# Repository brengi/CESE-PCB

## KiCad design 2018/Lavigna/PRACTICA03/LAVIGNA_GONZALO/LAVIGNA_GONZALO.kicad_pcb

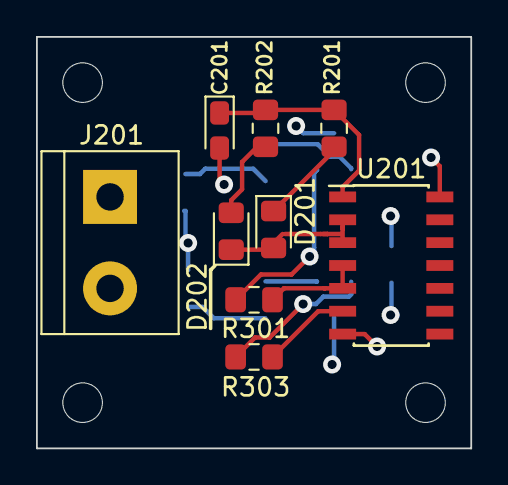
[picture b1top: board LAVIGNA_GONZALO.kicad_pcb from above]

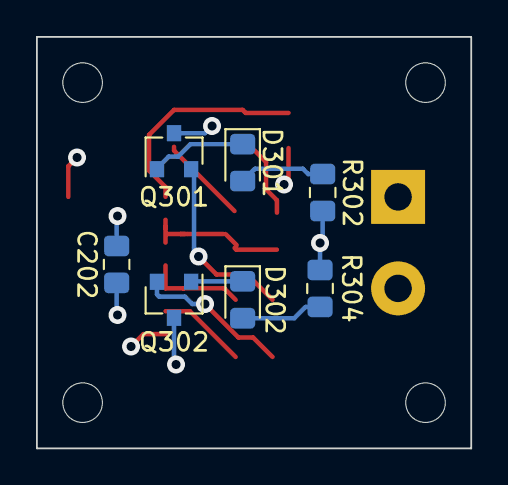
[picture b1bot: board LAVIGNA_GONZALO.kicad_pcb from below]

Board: 4 copper layers, 24.1 x 22.9 mm, 20 parts (7 on the bottom side), 14 nets.

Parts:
C201: CP; CP_EIA-2012-12_Kemet-R_Pad1.30x1.05mm_HandSolder
C202: 0.1u; C_0805_2012Metric_Pad1.15x1.40mm_HandSolder
D201, D202: 1N4148; D_0805_2012Metric_Pad1.15x1.40mm_HandSolder
D301, D302: LED ROJO; D_0805_2012Metric_Pad1.15x1.40mm_HandSolder
J201: Conn_01x02; TerminalBlock_bornier-2_P5.08mm
MH101, MH102, MH103, MH104: MountingHole; MountingHole_2.2mm_M2
Q301, Q302: BC546; SOT-23
R201, R202: 100K; R_0805_2012Metric_Pad1.15x1.40mm_HandSolder
R301, R303: 2K2; R_0805_2012Metric_Pad1.15x1.40mm_HandSolder
R302, R304: 470R; R_0805_2012Metric_Pad1.15x1.40mm_HandSolder
U201: 40106; SOIC-14_3.9x8.7mm_P1.27mm

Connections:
+5V: C202.1, J201.2, R302.2, R304.2, U201.14
/Circuito con leds/LED1: R301.2, U201.4, U201.5
/Circuito con leds/LED2: R303.2, U201.6
GND: C201.2, C202.2, J201.1, Q301.3, Q302.3, U201.7
unnamed: C201.1, R201.2, R202.2, U201.1
unnamed: D201.1, R201.1
unnamed: D201.2, D202.1, U201.2, U201.3
unnamed: D202.2, R202.1
unnamed: D301.1, Q301.1
unnamed: D301.2, R302.1
unnamed: D302.1, Q302.1
unnamed: D302.2, R304.1
unnamed: Q301.2, R301.1
unnamed: Q302.2, R303.1

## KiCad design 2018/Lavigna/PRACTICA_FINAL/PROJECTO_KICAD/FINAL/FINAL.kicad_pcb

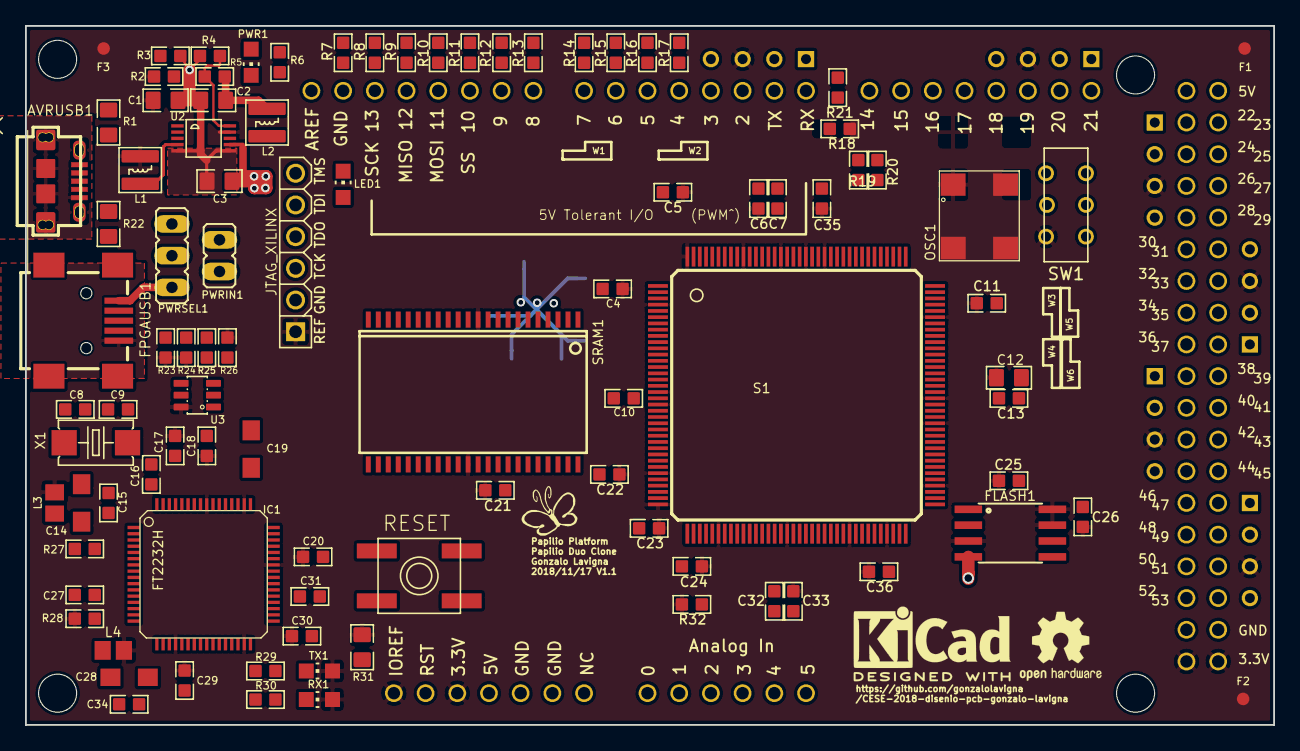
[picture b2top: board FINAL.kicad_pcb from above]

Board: 4 copper layers, 100.0 x 56.0 mm, 120 parts (0 on the bottom side), 160 nets.

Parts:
AVRUSB1: MYCON2_USB-MINI-B; CON2_USB_MICRO_B_AT
C1, C2: 22u/6V3; 0805
C3: 10uF/10V; 0805
C4, C5, C6, C7, C10, C11, C13, C15, C16, C17, C18, C20, C21, C22, C23, C24, C25, C26, C27, C29, C30, C31, C32, C33, C34, C35, C36: 0.1uF; 0603
C8, C9: 27pF; 0603
C12: 0.1uF; 0805
C14, C28: 4.7uF; SMC_A
C19: 3.3uF; SMC_A
C101, C102, C105: 100nF; 0603
C103, C104: 1uF; 0603
C106, C107: 22pF; 0603
F1, F2, F3: Fiducial; Fiducial_1mm_Dia_2mm_Outer
FLASH1: FLASH-SPI-25XXSMD1; SO08-EIAJ
FPGAUSB1: CONN_USB; CONN_USB_MINI-B
IC1: FT2232H; LQFP64
L1, L2: 3.3uH; VLS3015
L3, L4: FERRITE_BEAD603; FB603
L100: MH2029-300Y; 0805
LED1: Yellow; CHIP-LED0805
LOGO1: Logo_Open_Hardware_Small; OSHW-Logo2_7.3x6mm_SilkScreen
LOGO2: logo_glavigna; KiCad-Logo2_6mm_SilkScreen
OSC1: 32MHz; OSC1
PWR1: Green; CHIP-LED0805
PWRIN1: JP1E; JP1
PWRSEL1: JP2E; JP2
R1, R22: 22R; 0805
R2: 6K8 1%; 0603
R3, R4, R5: 1K5 1%; 0603
R6: 1K8; 0603
R7, R32: 4.7K; 0603
R8, R9, R10, R11, R12, R13, R14, R15, R16, R17, R18, R19, R20, R21: 390; 0603
R23, R24, R26, R28, R110: 10K; 0603
R25: 2.2K; 0603
R27: 12K 1%; 0603
R29, R30: 1K; 0603
R31: 47K; 0805
R109: 1M; 0603
RESET: EVQQ2; EVQ-Q2
RX1: LEDCHIP-LED0805; CHIP-LED0805
S1: 6SLX9TQG144; TQ144
SRAM1: ISSI_SRAM_8BIT; TSOP44-II
SW1: SWITCH-2CH-6P-3010010P1; 6P-2CH-2.54-9.1X3.5X3.2+2H
TX1: LEDCHIP-LED0805; CHIP-LED0805
U1: ARDUINO_MEGA_SHIELD
U2: LTC3419MS; MSOP10
U3: 93C56B; SOT23-6
U101: ATMEGA32U4-XUMU; QFN44ML7X7
U$1: JTAG_XILINX; JTAG
U$3, U$3#2, U$3#3, U$3#4: STAND-OFF-TIGHT
U$7: GADGETFACTORY_LOGO
WING_POWER1, WING_POWER2, WING_POWER3, WING_POWER4, WING_POWER5, WING_POWER6: FRAME-A4L-LOC; POWER_NO_TEXT
X1: 12MHz; 4X6
Y1: 16Mhz KX-7; CRYSTAL-3.2-2.5

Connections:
+1V2: C2.1, C7.1, C10.1, C13.1, C32.1, L2.2, R5.2, S1.19, S1.28, S1.52, S1.89, S1.128
+1V8: C16.1, C19.+, C27.1, C31.1, IC1.12, IC1.37, IC1.49, IC1.64
+3V3: C1.1, C4.1, C5.1, C6.1, C11.1, C12.1, C17.1, C18.1, C20.1, C21.1, C22.1, C23.1, C24.1, C25.1, C26.1, C29.1, C30.1, C33.1, C35.1, C36.1, C101.2, C105.2, FLASH1.3, FLASH1.7, FLASH1.8, IC1.20, IC1.31, IC1.42, IC1.50, IC1.56, L1.2, L3.2, L4.2, L100.2, OSC1.1@1, OSC1.4@4, R2.2, R23.1, R24.1, R26.1, R28.1, R31.2, R32.1, R110.2, RX1.A, S1.4, S1.18, S1.20, S1.31, S1.36, S1.42, S1.53, S1.63, S1.69, S1.76, S1.86, S1.90, S1.103, S1.122, S1.125, S1.129, S1.135, S1.144, SRAM1.11, SRAM1.33, SW1.CH2A, TX1.A, U1.3.3V, U1.3V3@1, U1.3V3@2, U1.IOREF, U2.9, U3.6, U101.2, U101.14, U101.34, U$1.JTAG_REF, WING_POWER1.P3, WING_POWER2.P3, WING_POWER3.P3, WING_POWER4.P3, WING_POWER5.P3, WING_POWER6.P3
+5V: C3.1, PWRIN1.1, PWRSEL1.2, R6.1, U1.5V@0, U1.5V@1, U1.5V@2, U2.2, U2.3, U2.7, WING_POWER1.P4, WING_POWER2.P4, WING_POWER3.P4, WING_POWER4.P4, WING_POWER5.P4, WING_POWER6.P4
/Arduino/5V_ARDUINO: AVRUSB1.P1, PWRSEL1.3, U101.7
/Arduino/ARD_RESET: R110.1, S1.139, U1.RES, U101.13
/Arduino/AREF: C102.1, U1.AREF, U101.42
/Arduino/ATMEGA_A0: U1.A0, U101.41
/Arduino/ATMEGA_A1: U1.A1, U101.40
/Arduino/ATMEGA_IO13*: R7.2, U101.9
/Arduino/AVCC: C104.1, L100.1, U101.24, U101.44
/Arduino/AVRUSB_N: R1.1, U101.3
/Arduino/AVRUSB_P: R22.1, U101.4
/Arduino/D+: AVRUSB1.P3, R22.2
/Arduino/D-: AVRUSB1.P2, R1.2
/Arduino/MEGA_D14: S1.115, U1.D14, U101.30
/Arduino/MEGA_D15: S1.114, U1.D15, U101.31
/Arduino/MEGA_D16: S1.112, U1.D16, U101.32
/Arduino/MEGA_D28/A5: S1.88, U1.A5, U1.D28, U101.36
/Arduino/MEGA_D30/A4: S1.85, U1.A4, U1.D30, U101.37
/Arduino/MEGA_D32/A3: S1.83, U1.A3, U1.D32, U101.38
/Arduino/MEGA_D34/A2: S1.81, U1.A2, U1.D34, U101.39
/Arduino/UCAP: C103.1, U101.6
/Arduino/XTAL1: C107.2, R109.1, U101.17, Y1.1
/Arduino/XTAL2: C106.2, R109.2, U101.16, Y1.3
/FPGA/AD0-JTAG_TCK: IC1.16, S1.109, U$1.JTAG_TCK
/FPGA/AD1-JTAG_TDI: IC1.17, S1.110, U$1.JTAG_TDI
/FPGA/AD2-JTAG_TDO: IC1.18, S1.106, U$1.JTAG_TDO
/FPGA/AD3-JTAG_TMS: IC1.19, S1.107, U$1.JTAG_TMS
/FPGA/AD4-DTR: IC1.21, S1.45
/FPGA/BD0_TXD/MPSSE_TCK: IC1.38, S1.46
/FPGA/BD1_RXD/MPSSE_TDI: IC1.39, S1.141
/FPGA/BD2_MPSSE_TDO: IC1.40, S1.140
/FPGA/BD3_MPSSE_TMS: IC1.41, S1.138
/FPGA/BD4-DTR: IC1.43, S1.137
/FPGA/FPGA-CORE/FLASH_CS: FLASH1.1, S1.38
/FPGA/FPGA-CORE/FLASH_SCK: FLASH1.6, S1.70
/FPGA/FPGA-CORE/FLASH_SI: FLASH1.5, S1.64
/FPGA/FPGA-CORE/FLASH_SO: FLASH1.2, S1.65
/FPGA/FPGA-CORE/MEGA_D0: R21.2, S1.116
/FPGA/FPGA-CORE/MEGA_D1: R20.2, S1.117
/FPGA/FPGA-CORE/MEGA_D2: R19.2, S1.118
/FPGA/FPGA-CORE/MEGA_D3: R18.2, S1.119
/FPGA/FPGA-CORE/MEGA_D4: R17.2, S1.120
/FPGA/FPGA-CORE/MEGA_D5: R16.2, S1.121
/FPGA/FPGA-CORE/MEGA_D6: R15.2, S1.123
/FPGA/FPGA-CORE/MEGA_D7: R14.2, S1.124
/FPGA/FPGA-CORE/MEGA_D8: R13.2, S1.126
/FPGA/FPGA-CORE/MEGA_D9: R12.2, S1.127
/FPGA/FPGA-CORE/MEGA_D10: R11.2, S1.131
/FPGA/FPGA-CORE/MEGA_D11: R10.2, S1.132
/FPGA/FPGA-CORE/MEGA_D12: R9.2, S1.133
/FPGA/FPGA-CORE/MEGA_D13: R8.2, S1.134
/FPGA/FPGA-CORE/MEGA_D17: S1.111, U1.D17
/FPGA/FPGA-CORE/MEGA_D18: S1.105, U1.D18
/FPGA/FPGA-CORE/MEGA_D19: S1.102, U1.D19
/FPGA/FPGA-CORE/MEGA_D20: S1.101, U1.D20
/FPGA/FPGA-CORE/MEGA_D21: S1.100, U1.D21
/FPGA/FPGA-CORE/MEGA_D22: S1.99, U1.D22
/FPGA/FPGA-CORE/MEGA_D23: S1.98, U1.D23
/FPGA/FPGA-CORE/MEGA_D24: S1.97, U1.D24
/FPGA/FPGA-CORE/MEGA_D25: S1.95, U1.D25
/FPGA/FPGA-CORE/MEGA_D26: S1.93, U1.D26
/FPGA/FPGA-CORE/MEGA_D27: S1.92, U1.D27
/FPGA/FPGA-CORE/MEGA_D29: S1.87, U1.D29
/FPGA/FPGA-CORE/MEGA_D31: S1.84, U1.D31
/FPGA/FPGA-CORE/MEGA_D33: S1.82, U1.D33
/FPGA/FPGA-CORE/MEGA_D35: S1.80, U1.D35
/FPGA/FPGA-CORE/MEGA_D36: S1.79, U1.D36
/FPGA/FPGA-CORE/MEGA_D37: S1.78, U1.D37
/FPGA/FPGA-CORE/MEGA_D38: S1.75, U1.D38
/FPGA/FPGA-CORE/MEGA_D39: S1.74, U1.D39
/FPGA/FPGA-CORE/MEGA_D40: S1.67, U1.D40
/FPGA/FPGA-CORE/MEGA_D41: S1.66, U1.D41
/FPGA/FPGA-CORE/MEGA_D42: S1.62, U1.D42
/FPGA/FPGA-CORE/MEGA_D43: S1.61, U1.D43
/FPGA/FPGA-CORE/MEGA_D44: S1.59, U1.D44
/FPGA/FPGA-CORE/MEGA_D45: S1.58, U1.D45
/FPGA/FPGA-CORE/MEGA_D46: S1.57, U1.D46
/FPGA/FPGA-CORE/MEGA_D47: S1.56, U1.D47
/FPGA/FPGA-CORE/MEGA_D48: S1.55, U1.D48
/FPGA/FPGA-CORE/MEGA_D49: S1.51, U1.D49
/FPGA/FPGA-CORE/MEGA_D50: S1.50, U1.D50
/FPGA/FPGA-CORE/MEGA_D51: S1.48, U1.D51
/FPGA/FPGA-CORE/MEGA_D52: S1.47, U1.D52
/FPGA/FPGA-CORE/MEGA_D53: R32.2, S1.39, U1.D53
/FPGA/FPGA-CORE/OSC_IN: OSC1.3@3, S1.94
/FPGA/FPGA-CORE/SRAM_A0: S1.7, SRAM1.3
/FPGA/FPGA-CORE/SRAM_A1: S1.8, SRAM1.4
/FPGA/FPGA-CORE/SRAM_A2: S1.9, SRAM1.5
/FPGA/FPGA-CORE/SRAM_A3: S1.10, SRAM1.6
/FPGA/FPGA-CORE/SRAM_A4: S1.11, SRAM1.7
/FPGA/FPGA-CORE/SRAM_A5: S1.5, SRAM1.16
/FPGA/FPGA-CORE/SRAM_A6: S1.2, SRAM1.17
/FPGA/FPGA-CORE/SRAM_A7: S1.1, SRAM1.18
/FPGA/FPGA-CORE/SRAM_A8: S1.143, SRAM1.19
/FPGA/FPGA-CORE/SRAM_A9: S1.142, SRAM1.20
/FPGA/FPGA-CORE/SRAM_A10: S1.43, SRAM1.26
/FPGA/FPGA-CORE/SRAM_A11: S1.41, SRAM1.27
/FPGA/FPGA-CORE/SRAM_A12: S1.40, SRAM1.28
/FPGA/FPGA-CORE/SRAM_A13: S1.35, SRAM1.29
/FPGA/FPGA-CORE/SRAM_A14: S1.34, SRAM1.30
/FPGA/FPGA-CORE/SRAM_A15: S1.27, SRAM1.38
/FPGA/FPGA-CORE/SRAM_A16: S1.29, SRAM1.39
/FPGA/FPGA-CORE/SRAM_A17: S1.33, SRAM1.40
/FPGA/FPGA-CORE/SRAM_A18: S1.32, SRAM1.41
/FPGA/FPGA-CORE/SRAM_A19: S1.44, SRAM1.25
/FPGA/FPGA-CORE/SRAM_A20: S1.30, SRAM1.42
/FPGA/FPGA-CORE/SRAM_D0: S1.14, SRAM1.9
/FPGA/FPGA-CORE/SRAM_D1: S1.15, SRAM1.10
/FPGA/FPGA-CORE/SRAM_D2: S1.16, SRAM1.13
/FPGA/FPGA-CORE/SRAM_D3: S1.17, SRAM1.14
/FPGA/FPGA-CORE/SRAM_D4: S1.21, SRAM1.31
/FPGA/FPGA-CORE/SRAM_D5: S1.22, SRAM1.32
/FPGA/FPGA-CORE/SRAM_D6: S1.23, SRAM1.35
/FPGA/FPGA-CORE/SRAM_D7: S1.24, SRAM1.36
/FPGA/FPGA-CORE/SW1: S1.104, SW1.COM2
/FPGA/FPGA-CORE/~SRAM_CS: S1.12, SRAM1.8
/FPGA/FPGA-CORE/~SRAM_OE: S1.26, SRAM1.37
/FPGA/FPGA-CORE/~SRAM_WE: S1.6, SRAM1.15
/FT2232H/5V_FT2232: FPGAUSB1.VUSB, PWRSEL1.1
/FT2232H/BC3: IC1.54, R30.2
/FT2232H/BC4: IC1.55, R29.2
/FT2232H/EECLK: IC1.62, U3.4
/FT2232H/EECS: IC1.63, R23.2, R24.2, U3.5
/FT2232H/EEDATA: IC1.61, R25.1, U3.3
/FT2232H/FTUSB_N: FPGAUSB1.D-, IC1.7
/FT2232H/FTUSB_P: FPGAUSB1.D+, IC1.8
/FT2232H/~RESET: IC1.14, R28.2
GND: AVRUSB1.P5, AVRUSB1.S1, AVRUSB1.S2, AVRUSB1.S3, AVRUSB1.S4, AVRUSB1.S5, AVRUSB1.S6, C1.2, C2.2, C3.2, C4.2, C6.2, C7.2, C8.2, C9.2, C10.2, C11.2, C12.2, C13.2, C14.-, C15.2, C16.2, C17.2, C18.2, C19.-, C20.2, C21.2, C23.2, C24.2, C25.2, C27.2, C28.-, C29.2, C30.2, C31.2, C32.2, C33.2, C34.2, C35.2, C101.1, C102.2, C103.2, C104.2, C105.1, C106.1, C107.1, FLASH1.4, FPGAUSB1.GND, IC1.1, IC1.5, IC1.10, IC1.11, IC1.13, IC1.15, IC1.25, IC1.35, IC1.47, IC1.51, LED1.C, OSC1.2@2, PWR1.C, PWRIN1.2, R3.2, R4.2, R27.2, RESET.B, RESET.B', S1.3, S1.13, S1.25, S1.49, S1.54, S1.60, S1.68, S1.73, S1.77, S1.91, S1.96, S1.108, S1.113, S1.130, S1.136, SRAM1.12, SRAM1.34, SW1.CH2B, U1.GND@0, U1.GND@1, U1.GND@2, U1.GND@3, U1.GND@4, U2.5, U2.6, U3.2, U101.5, U101.15, U101.23, U101.33, U101.35, U101.43, U101.EXP, WING_POWER1.P1, WING_POWER2.P1, WING_POWER3.P1, WING_POWER4.P1, WING_POWER5.P1, WING_POWER6.P1, Y1.2, Y1.4
unnamed: C8.1, IC1.3, X1.2
unnamed: C9.1, IC1.2, X1.1
unnamed: C14.+, C15.1, C28.+, C34.1, IC1.4, L3.1
unnamed: C5.2, C22.2, C26.2, C36.2
unnamed: IC1.6, R27.1
unnamed: IC1.9, L4.1
unnamed: L1.1, U2.4
unnamed: L2.1, U2.8
unnamed: LED1.A, R7.1
unnamed: PWR1.A, R6.2
unnamed: R2.1, R3.1, U2.1
unnamed: R4.1, R5.1, U2.10
unnamed: R8.1, U1.D13
unnamed: R9.1, U1.D12
unnamed: R10.1, U1.D11
unnamed: R11.1, U1.D10
unnamed: R12.1, U1.D9
unnamed: R13.1, U1.D8
unnamed: R14.1, U1.D7
unnamed: R15.1, U1.D6
unnamed: R16.1, U1.D5
unnamed: R17.1, U1.D4
unnamed: R18.1, U1.D3
unnamed: R19.1, U1.D2
unnamed: R20.1, U1.TX
unnamed: R21.1, U1.RX
unnamed: R25.2, R26.2, U3.1
unnamed: R29.1, TX1.C
unnamed: R30.1, RX1.C
unnamed: R31.1, RESET.A, RESET.A', S1.37

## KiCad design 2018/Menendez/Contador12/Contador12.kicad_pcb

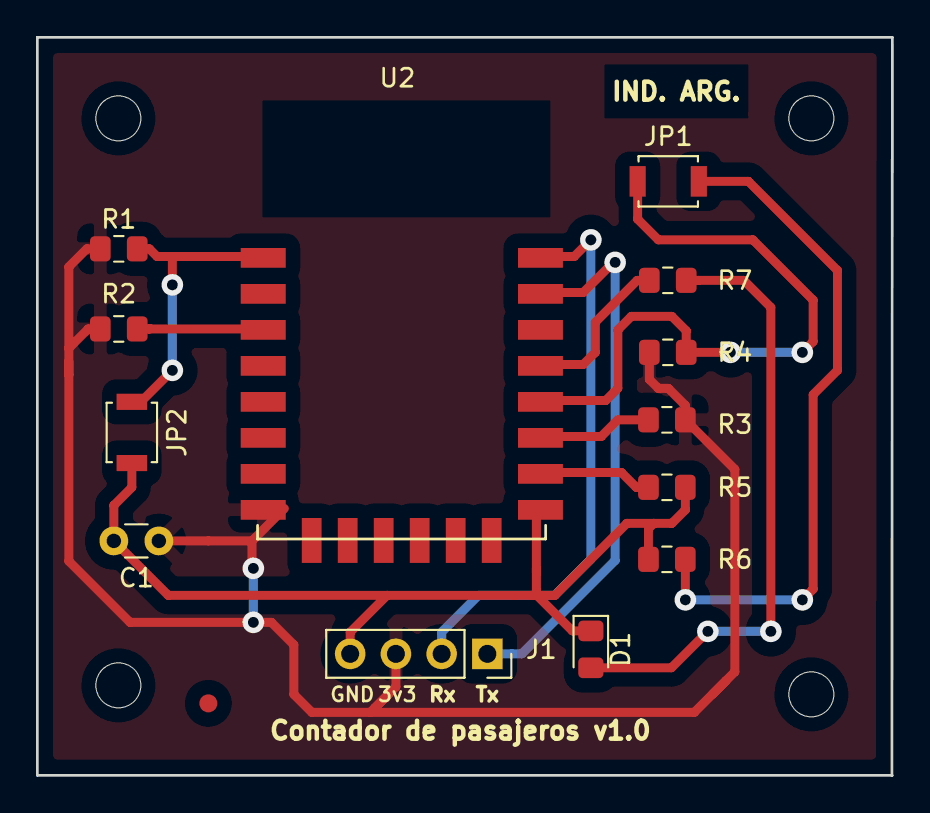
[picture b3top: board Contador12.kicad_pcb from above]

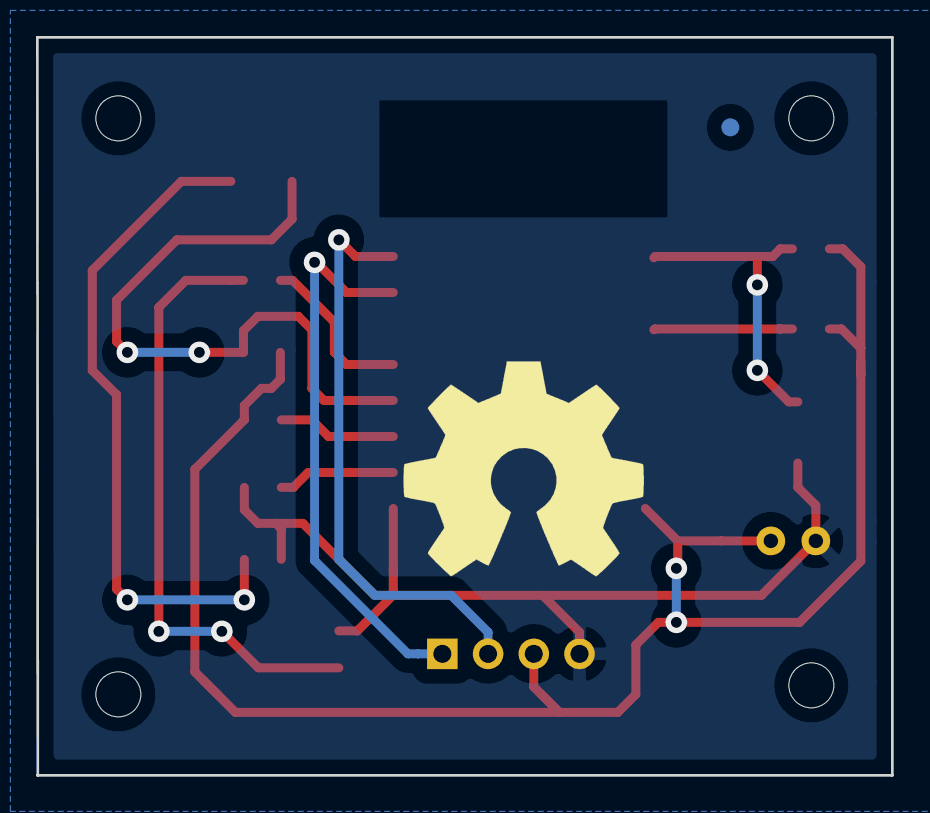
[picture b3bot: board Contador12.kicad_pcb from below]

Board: 2 copper layers, 47.5 x 41.0 mm, 20 parts (2 on the bottom side), 12 nets.

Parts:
C1: 100n; C_Disc_D3.0mm_W1.6mm_P2.50mm
D1: LED; LED_0805_2012Metric_Pad1.15x1.40mm_HandSolder
F1, F2: MH2; Fiducial_1mm_Dia_2mm_Outer
J1: Conector_ESP; PinSocket_1x04_P2.54mm_Vertical
JP1, JP2: Jumper; SW_SPST_B3U-1000P
Logo1: Logo_Open_Hardware_Small; OSHW-Symbol_13.4x12mm_SilkScreen
MH1: MH1; MountingHole_2.5mm
MH2: MH2; MountingHole_2.5mm
MH3: MH3; MountingHole_2.5mm
MH4: MH4; MountingHole_2.5mm
R1, R2, R3, R4, R5: 10k; R_0805_2012Metric_Pad1.15x1.40mm_HandSolder
R6, R7: 470; R_0805_2012Metric_Pad1.15x1.40mm_HandSolder
U2: ESP-12E; ESP-12E_SMD

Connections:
+3V3: C1.1, J1.3, R1.1, R2.2, R3.2, R4.1, U2.8
/Program: JP1.1, R4.2, U2.12
/Reset: JP2.1, R1.2, U2.1
/Rx: J1.2, U2.16
/Tx: J1.1, U2.15
GND: C1.2, D1.1, J1.4, JP2.2, R5.2, R6.2, U2.9
unnamed: D1.2, R7.2
unnamed: JP1.2, R6.1
unnamed: R2.1, U2.3
unnamed: R3.1, U2.11
unnamed: R5.1, U2.10
unnamed: R7.1, U2.13

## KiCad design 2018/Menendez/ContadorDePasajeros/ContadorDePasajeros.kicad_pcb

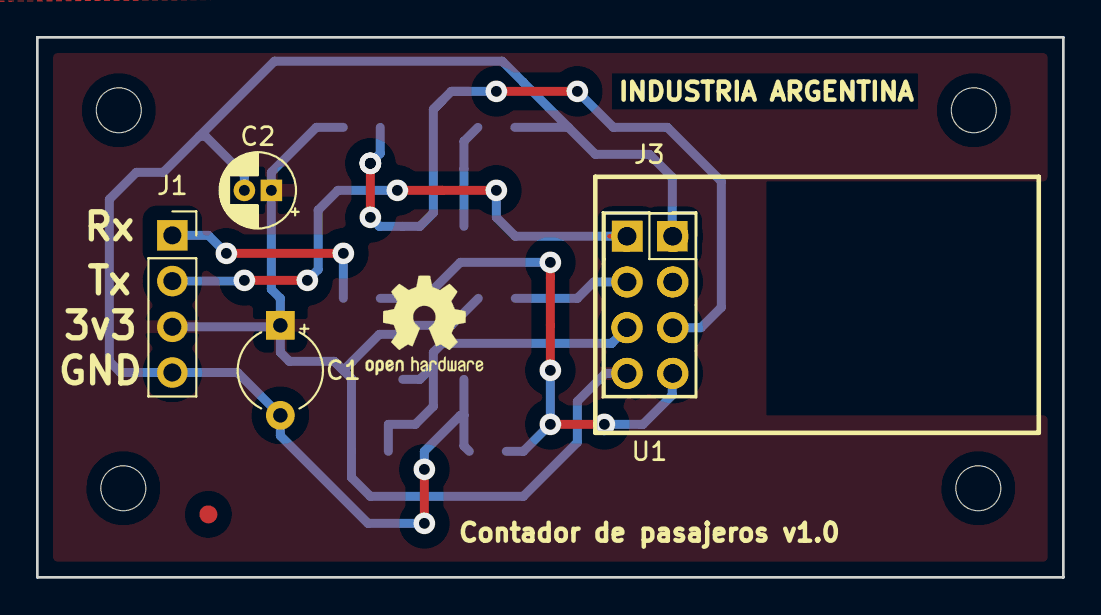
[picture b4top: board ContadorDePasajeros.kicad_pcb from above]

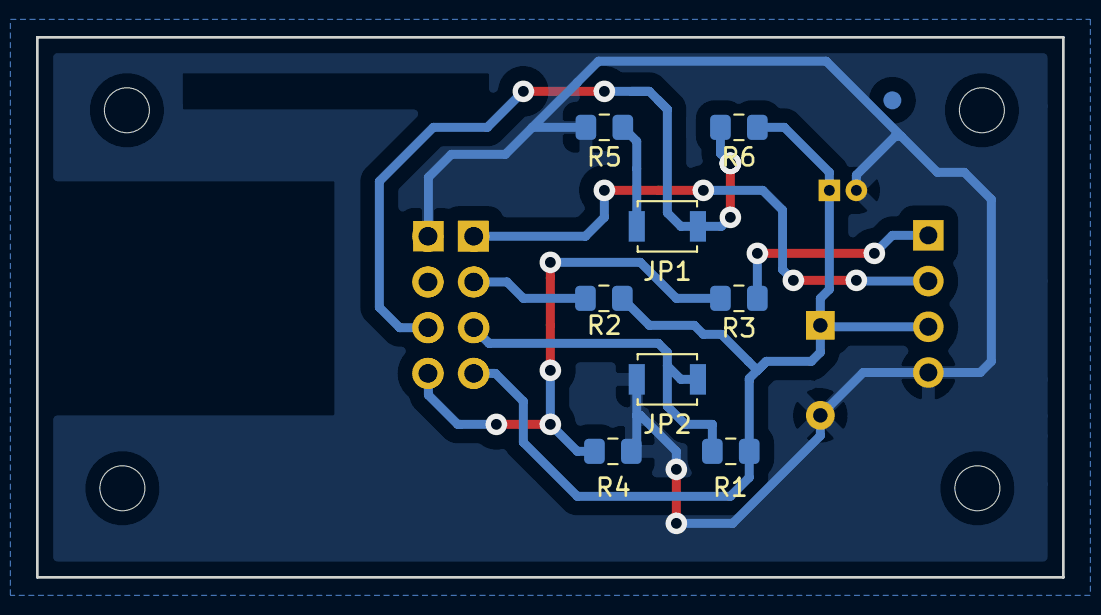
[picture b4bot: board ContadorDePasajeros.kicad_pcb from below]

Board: 2 copper layers, 57.0 x 30.0 mm, 20 parts (9 on the bottom side), 10 nets.

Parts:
C1: 100n; CP_Radial_Tantal_D4.5mm_P5.00mm
C2: 100u; CP_Radial_D4.0mm_P1.50mm
F1, F2: MH4; Fiducial_1mm_Dia_2mm_Outer
J1: Conector_in; PinSocket_1x04_P2.54mm_Vertical
J3: Conector_esp; PinSocket_2x04_P2.54mm_Vertical
JP1, JP2: Jumper; SW_SPST_B3U-1000P
Logo1: Logo_Open_Hardware_Small; OSHW-Logo2_7.3x6mm_SilkScreen
MH1: MH1; MountingHole_2.5mm
MH2: MH2; MountingHole_2.5mm
MH3: MH3; MountingHole_2.5mm
MH4: MH4; MountingHole_2.5mm
R1, R2, R6: 3k3; R_0805_2012Metric_Pad1.15x1.40mm_HandSolder
R3: 1k; R_0805_2012Metric_Pad1.15x1.40mm_HandSolder
R4: 2k; R_0805_2012Metric_Pad1.15x1.40mm_HandSolder
R5: 470; R_0805_2012Metric_Pad1.15x1.40mm_HandSolder
U1: ESP01; ESP-01

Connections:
+3V3: C1.1, C2.1, J1.3, J3.8, R1.2, R2.2, R6.1, U1.7
/Ch: J3.4, R2.1, U1.3
/Gpio0: J3.5, JP1.1, R6.2, U1.6
/Gpio2: J3.3, U1.4
/Rs: J3.6, JP2.1, R1.1, U1.5
/Rx_i: J3.7, R3.2, R4.1, U1.8
GND: C1.2, C2.2, J1.4, J3.1, JP2.2, R4.2, R5.2, U1.2
unnamed: JP1.2, R5.1
Rx: J1.1, R3.1
Tx: J1.2, J3.2, U1.1

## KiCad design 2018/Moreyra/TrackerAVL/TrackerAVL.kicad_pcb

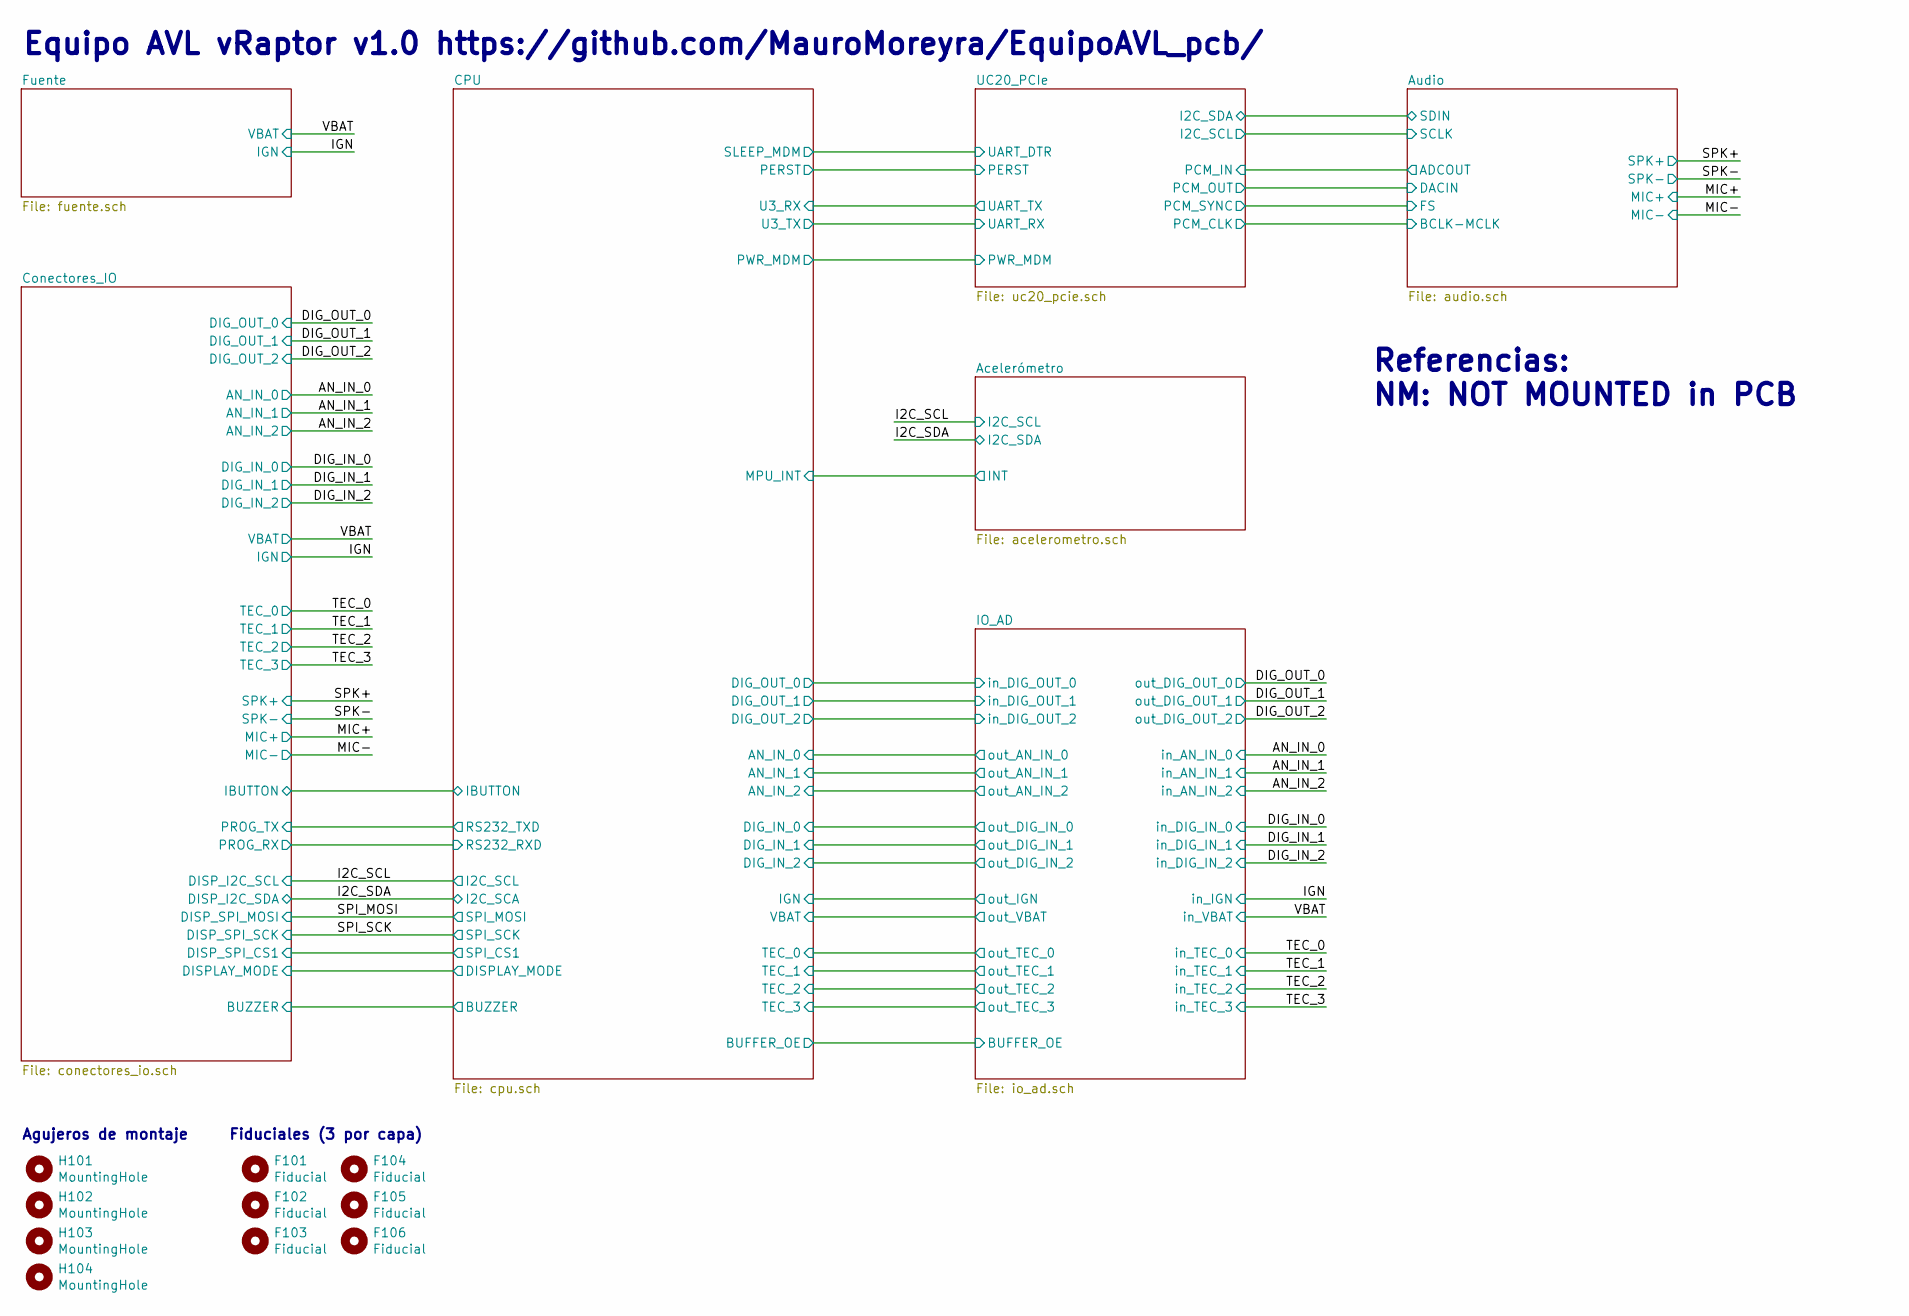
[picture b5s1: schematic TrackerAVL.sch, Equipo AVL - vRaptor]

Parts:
F101, F102, F103, F104, F105, F106: Fiducial; Fiducial_1mm_Dia_2mm_Outer
H101, H102, H103, H104: MountingHole; MountingHole_3.2mm_M3

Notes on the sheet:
Equipo AVL vRaptor v1.0 https://github.com/MauroMoreyra/EquipoAVL_pcb/
Referencias: NM: NOT MOUNTED in PCB
Agujeros de montaje
Fiduciales (3 por capa)

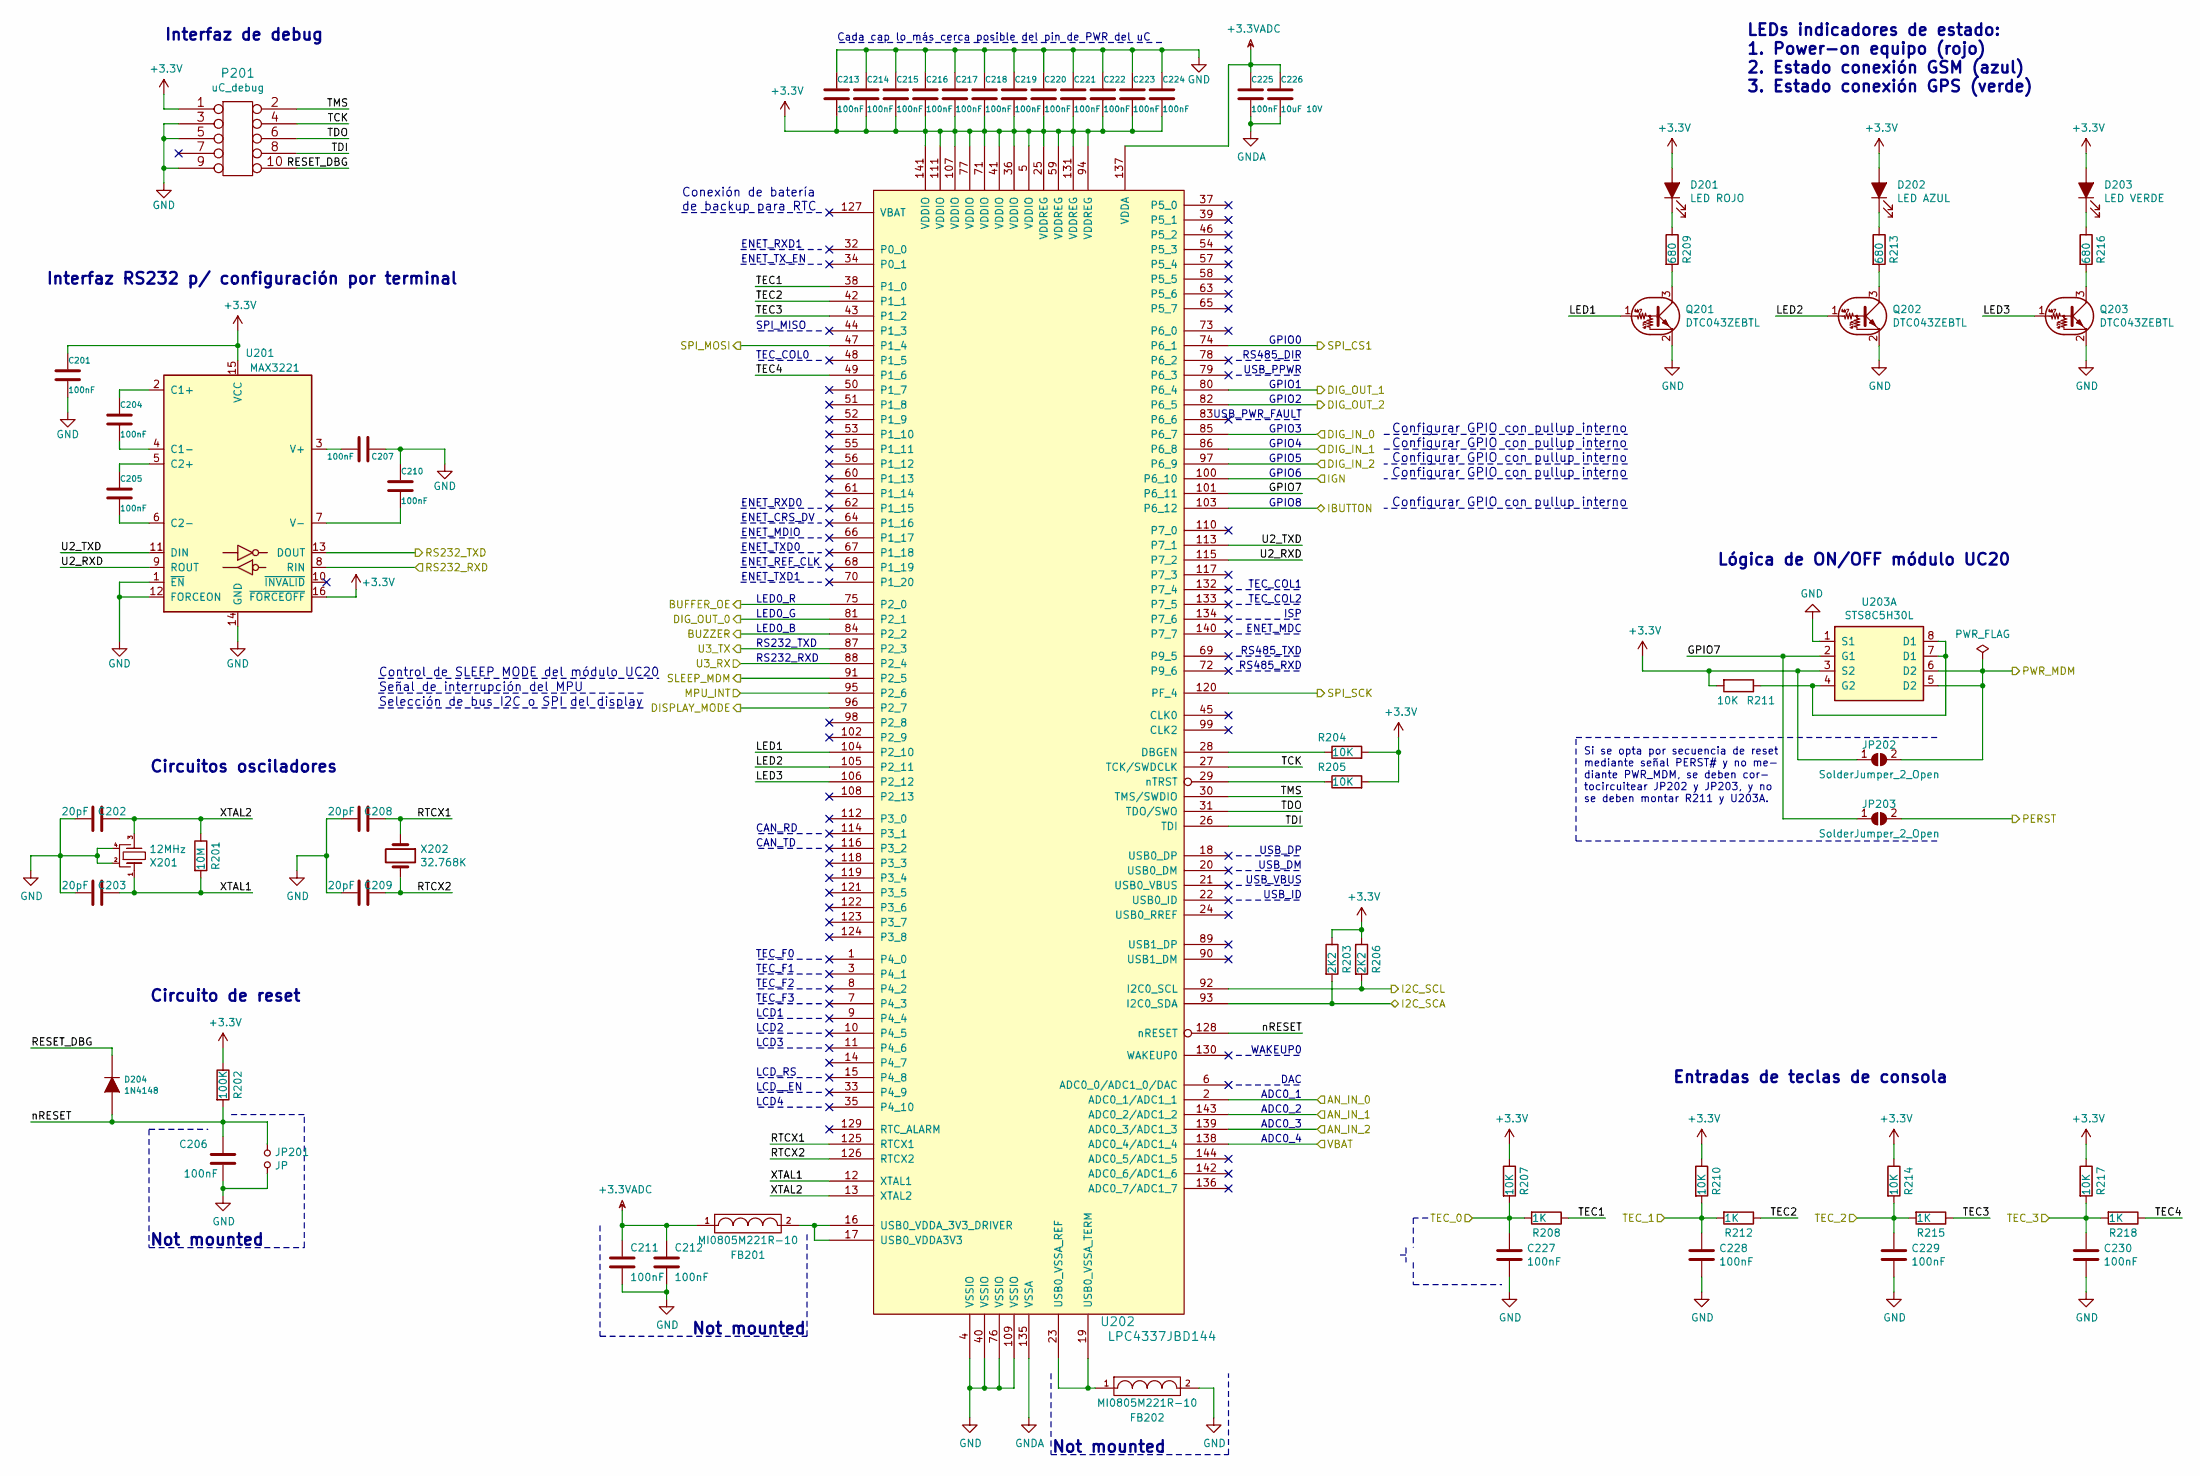
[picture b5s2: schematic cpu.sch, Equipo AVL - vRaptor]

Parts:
C201, C204, C205, C206, C207, C210, C211, C212, C213, C214, C215, C216, C217, C218, C219, C220, C221, C222, C223, C224, C225, C227, C228, C229, C230: 100nF; C_0805_2012Metric_Pad1.15x1.40mm_HandSolder
C202, C203, C208, C209: 20pF; C_0805_2012Metric_Pad1.15x1.40mm_HandSolder
C226: 10uF 10V; C_1206_3216Metric_Pad1.42x1.75mm_HandSolder
D201: LED ROJO; LED_0805_2012Metric_Pad1.15x1.40mm_HandSolder
D202: LED AZUL; LED_0805_2012Metric_Pad1.15x1.40mm_HandSolder
D203: LED VERDE; LED_0805_2012Metric_Pad1.15x1.40mm_HandSolder
D204: 1N4148; D_SOD-123
FB201, FB202: MI0805M221R-10; L_0805_2012Metric_Pad1.15x1.40mm_HandSolder
JP201: JP; PinHeader_1x02_P2.54mm_Vertical
JP202, JP203: SolderJumper_2_Open; SolderJumper-2_P1.3mm_Open_Pad1.0x1.5mm
P201: uC_debug; Pin_Array_5x2_1.27mm_SMD
Q201, Q202, Q203: DTC043ZEBTL; SOT-523_(SOT-416)
R201: 10M; R_0805_2012Metric_Pad1.15x1.40mm_HandSolder
R202: 100K; R_0805_2012Metric_Pad1.15x1.40mm_HandSolder
R203, R206: 2K2; R_0805_2012Metric_Pad1.15x1.40mm_HandSolder
R204, R205, R207, R210, R211, R214, R217: 10K; R_0805_2012Metric_Pad1.15x1.40mm_HandSolder
R208, R212, R215, R218: 1K; R_0805_2012Metric_Pad1.15x1.40mm_HandSolder
R209, R213, R216: 680; R_0805_2012Metric_Pad1.15x1.40mm_HandSolder
U201: MAX3221; SSOP-16_5.3x6.2mm_P0.65mm
U202: LPC4337JBD144; LQFP144-M05
U203: STS8C5H30L; SOIC-8_3.9x4.9mm_P1.27mm
X201: 12MHz; FA238V-XTAL; Digikey/Mouser 887-1831-1-ND
X202: 32.768K; 32.768-XTAL-SMD

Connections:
+3.3VADC: C211.1, C212.1, C225.1, C226.1, FB201.1, U202.137 (VDDA); also elsewhere on the board
+3V3: C201.1, C213.2, C214.2, C215.2, C216.2, C217.2, C218.2, C219.2, C220.2, C221.2, C222.2, C223.2, C224.2, D201.2 (A), D202.2 (A), D203.2 (A), JP202.1 (A), P201.1, R202.1, R203.1, R204.2, R205.2, R206.1, R207.1, R210.1, R211.2, R214.1, R217.1, U201.15 (VCC), U201.16 (~FORCEOFF), U202.5 (VDDIO), U202.25 (VDDREG), U202.36 (VDDIO), U202.41 (VDDIO), U202.59 (VDDREG), U202.71 (VDDIO), U202.77 (VDDIO), U202.94 (VDDREG), U202.107 (VDDIO), U202.111 (VDDIO), U202.131 (VDDREG), U202.141 (VDDIO), U203.3 (S2); also elsewhere on the board
/Acelerómetro/INT: U202.95 (P2_6); also elsewhere on the board
/CPU/AN_IN_0: U202.2 (ADC0_1/ADC1_1); also elsewhere on the board
/CPU/AN_IN_1: U202.143 (ADC0_2/ADC1_2); also elsewhere on the board
/CPU/AN_IN_2: U202.139 (ADC0_3/ADC1_3); also elsewhere on the board
/CPU/BUFFER_OE: U202.75 (P2_0); also elsewhere on the board
/CPU/BUZZER: U202.84 (P2_2); also elsewhere on the board
/CPU/DIG_IN_0: U202.85 (P6_7); also elsewhere on the board
/CPU/DIG_IN_1: U202.86 (P6_8); also elsewhere on the board
/CPU/DIG_IN_2: U202.97 (P6_9); also elsewhere on the board
/CPU/DIG_OUT_0: U202.81 (P2_1); also elsewhere on the board
/CPU/DIG_OUT_1: U202.80 (P6_4); also elsewhere on the board
/CPU/DIG_OUT_2: U202.82 (P6_5); also elsewhere on the board
/CPU/DISPLAY_MODE: U202.96 (P2_7); also elsewhere on the board
/CPU/GPIO7: JP203.1 (A), U202.101 (P6_11), U203.2 (G1)
/CPU/IBUTTON: U202.103 (P6_12); also elsewhere on the board
/CPU/IGN: U202.100 (P6_10); also elsewhere on the board
/CPU/LED1: Q201.1 (B), U202.104 (P2_10)
/CPU/LED2: Q202.1 (B), U202.105 (P2_11)
/CPU/LED3: Q203.1 (B), U202.106 (P2_12)
/CPU/PERST: JP203.2 (B); also elsewhere on the board
/CPU/PWR_MDM: JP202.2 (B), U203.5 (D2), U203.6 (D2); also elsewhere on the board
/CPU/RESET_DBG: D204.2 (K), P201.10
/CPU/RTCX1: C208.1, U202.125 (RTCX1), X202.1
/CPU/RTCX2: C209.1, U202.126 (RTCX2), X202.2
/CPU/SLEEP_MDM: U202.91 (P2_5); also elsewhere on the board
/CPU/TCK: P201.4, U202.27 (TCK/SWDCLK)
/CPU/TDI: P201.8, U202.26 (TDI)
/CPU/TDO: P201.6, U202.31 (TDO/SWO)
/CPU/TEC1: R208.1, U202.38 (P1_0)
/CPU/TEC2: R212.1, U202.42 (P1_1)
/CPU/TEC3: R215.1, U202.43 (P1_2)
/CPU/TEC4: R218.1, U202.49 (P1_6)
/CPU/TEC_0: C227.1, R207.2, R208.2; also elsewhere on the board
/CPU/TEC_1: C228.1, R210.2, R212.2; also elsewhere on the board
/CPU/TEC_2: C229.1, R214.2, R215.2; also elsewhere on the board
/CPU/TEC_3: C230.1, R217.2, R218.2; also elsewhere on the board
/CPU/TMS: P201.2, U202.30 (TMS/SWDIO)
/CPU/U2_RXD: U201.9 (ROUT), U202.115 (P7_2)
/CPU/U2_TXD: U201.11 (DIN), U202.113 (P7_1)
/CPU/U3_RX: U202.88 (P2_4); also elsewhere on the board
/CPU/U3_TX: U202.87 (P2_3); also elsewhere on the board
/CPU/VBAT: U202.138 (ADC0_4/ADC1_4); also elsewhere on the board
/CPU/XTAL1: C203.1, R201.2, U202.12 (XTAL1), X201.1 (A)
/CPU/XTAL2: C202.1, R201.1, U202.13 (XTAL2), X201.3 (B)
/CPU/nRESET: C206.1, D204.1 (A), JP201.1, R202.2, U202.128 (nRESET)
/Conectores_IO/DISP_SPI_CS1: U202.74 (P6_1); also elsewhere on the board
/Conectores_IO/PROG_RX: U201.8 (RIN); also elsewhere on the board
/Conectores_IO/PROG_TX: U201.13 (DOUT); also elsewhere on the board
/I2C_SCL: R206.2, U202.92 (I2C0_SCL); also elsewhere on the board
/I2C_SDA: R203.2, U202.93 (I2C0_SDA); also elsewhere on the board
/SPI_MOSI: U202.47 (P1_4); also elsewhere on the board
/SPI_SCK: U202.120 (PF_4); also elsewhere on the board
GND: C201.2, C202.2, C203.2, C206.2, C207.1, C208.2, C209.2, C210.1, C211.2, C212.2, C213.1, C214.1, C215.1, C216.1, C217.1, C218.1, C219.1, C220.1, C221.1, C222.1, C223.1, C224.1, C227.2, C228.2, C229.2, C230.2, FB202.2, JP201.2, P201.3, P201.5, P201.9, Q201.2 (E), Q202.2 (E), Q203.2 (E), U201.1 (~EN), U201.12 (FORCEON), U201.14 (GND), U202.4 (VSSIO), U202.40 (VSSIO), U202.76 (VSSIO), U202.109 (VSSIO), U203.1 (S1), X201.2 (GND), X201.4 (GND); also elsewhere on the board
GNDA: C225.2, C226.2, U202.135 (VSSA); also elsewhere on the board
unnamed: C204.1, U201.2 (C1+)
unnamed: C204.2, U201.4 (C1-)
unnamed: C205.1, U201.5 (C2+)
unnamed: C205.2, U201.6 (C2-)
unnamed: C207.2, U201.3 (V+)
unnamed: C210.2, U201.7 (V-)
unnamed: D201.1 (K), R209.1
unnamed: D202.1 (K), R213.1
unnamed: D203.1 (K), R216.1
unnamed: FB201.2, U202.16 (USB0_VDDA_3V3_DRIVER), U202.17 (USB0_VDDA3V3)
unnamed: FB202.1, U202.19 (USB0_VSSA_TERM), U202.23 (USB0_VSSA_REF)
unnamed: Q201.3 (C), R209.2
unnamed: Q202.3 (C), R213.2
unnamed: Q203.3 (C), R216.2
unnamed: R204.1, U202.28 (DBGEN)
unnamed: R205.1, U202.29 (nTRST)
unnamed: R211.1, U203.4 (G2), U203.7 (D1), U203.8 (VSS)

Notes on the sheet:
Configurar GPIO con pullup interno
LEDs indicadores de estado: 1. Power-on equipo (rojo) 2. Estado conexión GSM (azul) 3. Estado conexión GPS (verde)
Entradas de teclas de consola
WAKEUP0
USB_PWR_FAULT
USB_PPWR
RS485_DIR
TEC_COL2
TEC_COL1
CAN_RD
CAN_TD
TEC_F0
TEC_F1
TEC_F2
TEC_F3
LCD1
LCD2
LCD3
LCD_RS
LCD__EN
LCD4
Circuitos osciladores
Not mounted
ENET_TXD1
ENET_REF_CLK
ENET_TXD0
ENET_MDIO
ENET_CRS_DV
ENET_RXD0
TEC_COL0
ENET_TX_EN
ENET_RXD1
Conexión de batería de backup para RTC
ENET_MDC
ISP
RS485_TXD
RS485_RXD
Interfaz de debug
DAC
Circuito de reset

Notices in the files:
parts and their libraries:
Copyright 2016 Accelerated Designs. All rights reserved.
